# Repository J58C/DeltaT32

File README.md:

# DeltaT32 – ESP32-C3 Wearable for Capstone

**DeltaT32** is a modular hardware design project based on the **ESP32-C3 Mini-1**, intended primarily for wearable systems, but versatile enough for general-purpose embedded applications. Created using **KiCad 8**, this project includes a main ESP unit and two detachable sensor boards (BMI160/270 and MPU9250), making it ideal for both academic and practical applications.

This design has been created specifically to fulfill the requirements of a **Capstone Project**, integrating modern hardware design practices with real-world applications. Although firmware development is still pending, the hardware is designed to be compatible with the **[esp-rs (ESP32 Rust)](https://github.com/esp-rs)** ecosystem.

## Project Structure

```
DeltaT32/
├── Schematic/ # PDF-format schematics
├── Hardwares/
│ ├── esp-unit-c3-v3/ # KiCad project for the main ESP32-C3 board
│ ├── sensor-bmi-v2/ # KiCad project for the BMI160/270 sensor board
│ └── sensor-mpu-v2/ # KiCad project for the MPU9250 sensor board
├── 3DModels/ # 3D models of components (if available)
├── Archives/ # Archived ZIP files of older versions
├── Materials/ # Bill of Materials (BOM) for each board
└── README.md # Project documentation
````

## Technical Specifications

| Component      | Description                                  |
|----------------|----------------------------------------------|
| MCU            | ESP32-C3 Mini-1                              |
| Sensors        | BMI160/270, MPU9250 (modular and detachable) |
| Design Style   | Modular: separate mainboard and sensor units |
| CAD Tool       | KiCad 8                                      |
| Firmware       | Not included (hardware only)                 |
| Rust Support   | Designed with esp-rs compatibility in mind   |
| Outputs        | Schematics, BOMs, 3D Visuals        |

## Firmware Compatibility

This hardware is designed to be compatible with the **[esp-rs (Rust for ESP32)](https://github.com/esp-rs)** ecosystem, but **no actual firmware has been implemented or tested** using Rust at this time. Custom firmware development in C, C++, or Rust.

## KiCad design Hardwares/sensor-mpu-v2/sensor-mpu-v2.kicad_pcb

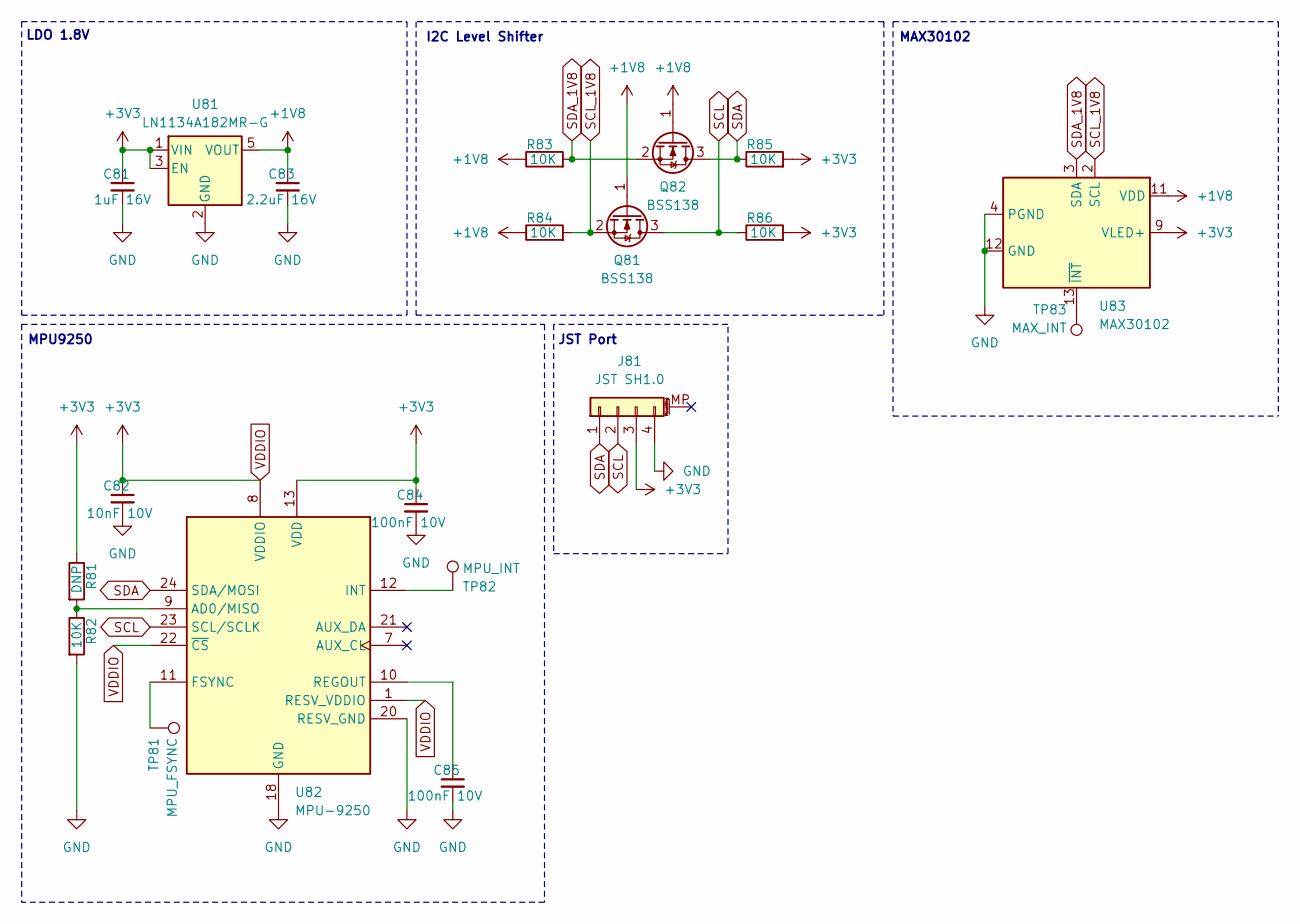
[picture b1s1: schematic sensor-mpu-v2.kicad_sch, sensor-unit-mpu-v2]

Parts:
C81: 1uF 16V; C_0603_1608Metric; LCSC C52923
C82: 10nF 10V; C_0603_1608Metric; LCSC C15195
C83: 2.2uF 16V; C_0603_1608Metric; LCSC C23630
C84, C85: 100nF 10V; C_0603_1608Metric; LCSC C1525
J81: JST SH1.0; JST_SH_BM04B-SRSS-TB_1x04-1MP_P1.00mm_Vertical
Q81, Q82: BSS138; SOT-23; LCSC C52895
R81: DNP; R_0402_1005Metric
R82, R83, R84, R85, R86: 10K; R_0402_1005Metric; LCSC C25744
TP81: MPU_FSYNC; TestPoint_Pad_D1.0mm
TP82: MPU_INT; TestPoint_Pad_D1.0mm
TP83: MAX_INT; TestPoint_Pad_D1.0mm
U81: LN1134A182MR-G; SOT-23-5; LCSC C141424
U82: MPU-9250; InvenSense_QFN-24_3x3mm_P0.4mm_NoMask
U83: MAX30102; Maxim_OLGA-14_3.3x5.6mm_P0.8mm

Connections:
+1V8: C83.1, Q81.1 (G), Q82.1 (G), R83.1, R84.1, U81.5 (VOUT), U83.11 (VDD)
GND: C81.2, C82.2, C83.2, C84.2, C85.2, J81.4, R82.2, U81.2 (GND), U82.18 (GND), U82.20 (RESV_GND), U83.4 (PGND), U83.12 (GND)
unnamed: R81.2, R82.1, U82.9 (AD0/MISO)
unnamed: TP81.1, U82.11 (FSYNC)
unnamed: TP82.1, U82.12 (INT)
unnamed: C85.1, U82.10 (REGOUT)
unnamed: TP83.1, U83.13 (~INT)
SCL: J81.2, Q81.3 (D), R86.1, U82.23 (SCL/SCLK)
SCL_1V8: Q81.2 (S), R84.2, U83.2 (SCL)
SDA: J81.1, Q82.3 (D), R85.1, U82.24 (SDA/MOSI)
SDA_1V8: Q82.2 (S), R83.2, U83.3 (SDA)
VDDIO: C81.1, C82.1, C84.1, J81.3, R81.1, R85.2, R86.2, U81.1 (VIN), U81.3 (EN), U82.1 (RESV_VDDIO), U82.8 (VDDIO), U82.13 (VDD), U82.22 (~CS), U83.9 (VLED+), U83.10 (VLED+)

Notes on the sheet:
I2C Level Shifter
MPU9250
MAX30102
JST Port
LDO 1.8V

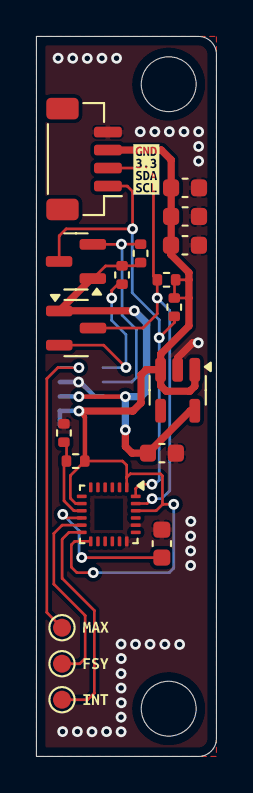
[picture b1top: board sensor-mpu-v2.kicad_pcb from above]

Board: 2 copper layers, 10.0 x 40.0 mm, 24 parts (1 on the bottom side), 12 nets.

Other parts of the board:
kibuzzard-680F6A44: G***; kibuzzard-680F6A44
kibuzzard-6817376F: G***; kibuzzard-6817376F
kibuzzard-6817407C: G***; kibuzzard-6817407C
kibuzzard-68174073: G***; kibuzzard-68174073

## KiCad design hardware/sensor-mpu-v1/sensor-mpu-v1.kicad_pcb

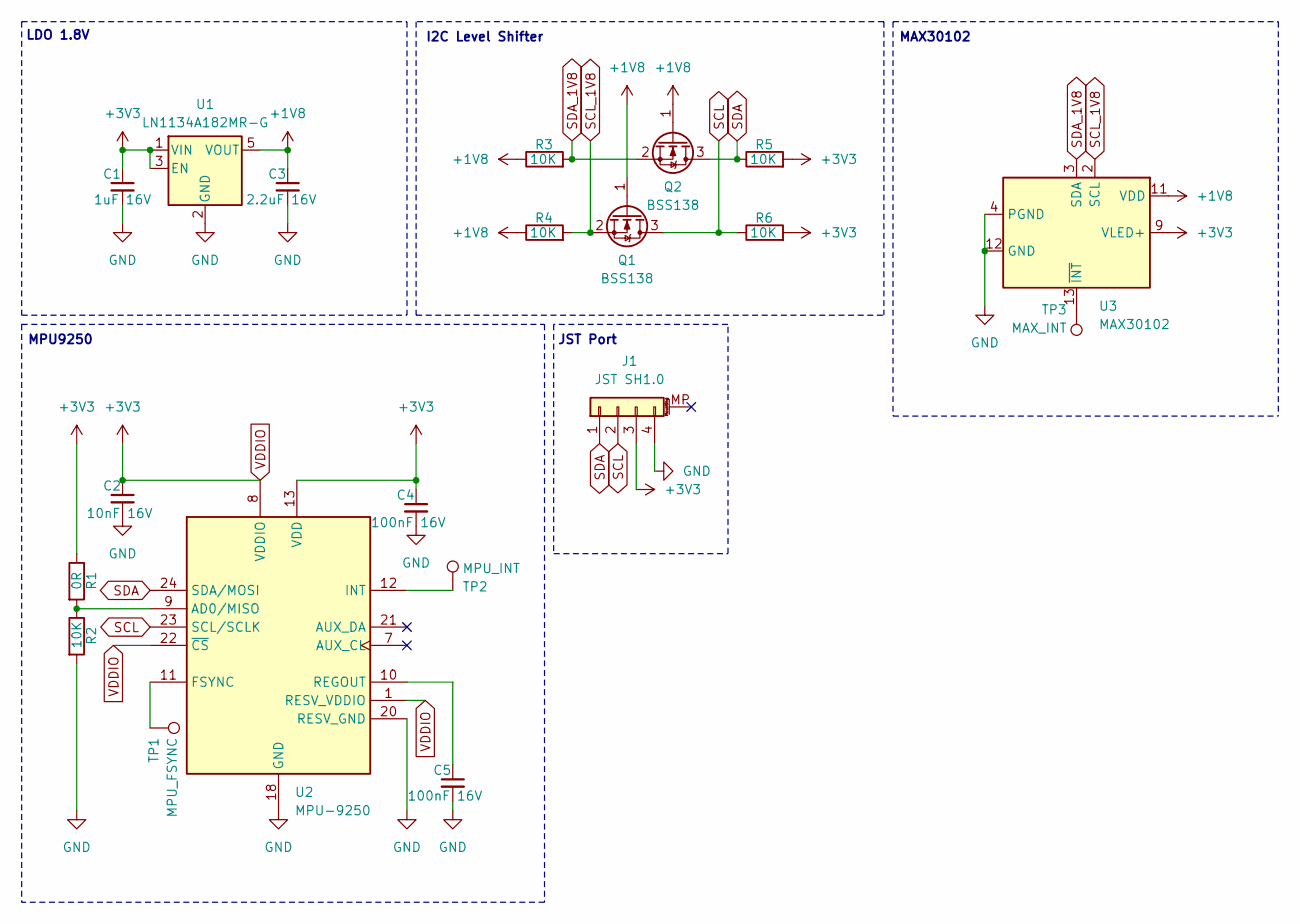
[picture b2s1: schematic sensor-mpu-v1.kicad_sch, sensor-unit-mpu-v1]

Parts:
C1: 1uF 16V; C_0603_1608Metric
C2: 10nF 16V; C_0603_1608Metric
C3: 2.2uF 16V; C_0603_1608Metric
C4, C5: 100nF 16V; C_0603_1608Metric
J1: JST SH1.0; JST_SH_SM04B-SRSS-TB_1x04-1MP_P1.00mm_Horizontal
Q1, Q2: BSS138; SOT-23
R1: 0R; R_0402_1005Metric
R2, R3, R4, R5, R6: 10K; R_0402_1005Metric
TP1: MPU_FSYNC; TestPoint_Pad_D1.0mm
TP2: MPU_INT; TestPoint_Pad_D1.0mm
TP3: MAX_INT; TestPoint_Pad_D1.0mm
U1: LN1134A182MR-G; SOT-23-5
U2: MPU-9250; InvenSense_QFN-24_3x3mm_P0.4mm_NoMask
U3: MAX30102; Maxim_OLGA-14_3.3x5.6mm_P0.8mm

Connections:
+1V8: C3.1, Q1.1 (G), Q2.1 (G), R3.1, R4.1, U1.5 (VOUT), U3.11 (VDD)
GND: C1.2, C2.2, C3.2, C4.2, C5.2, J1.4, R2.2, U1.2 (GND), U2.18 (GND), U2.20 (RESV_GND), U3.4 (PGND), U3.12 (GND)
unnamed: R1.2, R2.1, U2.9 (AD0/MISO)
unnamed: TP1.1, U2.11 (FSYNC)
unnamed: TP2.1, U2.12 (INT)
unnamed: C5.1, U2.10 (REGOUT)
unnamed: TP3.1, U3.13 (~INT)
SCL: J1.2, Q1.3 (D), R6.1, U2.23 (SCL/SCLK)
SCL_1V8: Q1.2 (S), R4.2, U3.2 (SCL)
SDA: J1.1, Q2.3 (D), R5.1, U2.24 (SDA/MOSI)
SDA_1V8: Q2.2 (S), R3.2, U3.3 (SDA)
VDDIO: C1.1, C2.1, C4.1, J1.3, R1.1, R5.2, R6.2, U1.1 (VIN), U1.3 (EN), U2.1 (RESV_VDDIO), U2.8 (VDDIO), U2.13 (VDD), U2.22 (~CS), U3.9 (VLED+), U3.10 (VLED+)

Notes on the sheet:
I2C Level Shifter
MPU9250
MAX30102
JST Port
LDO 1.8V

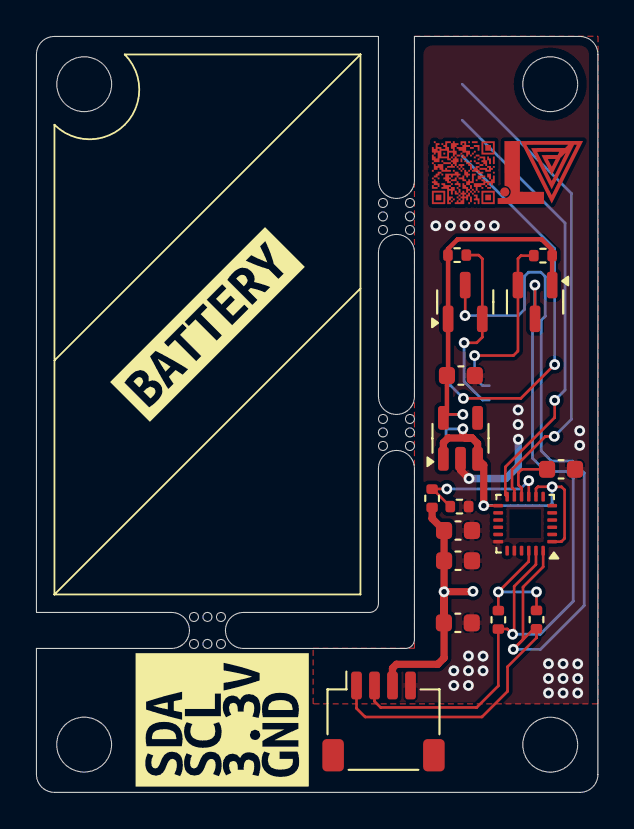
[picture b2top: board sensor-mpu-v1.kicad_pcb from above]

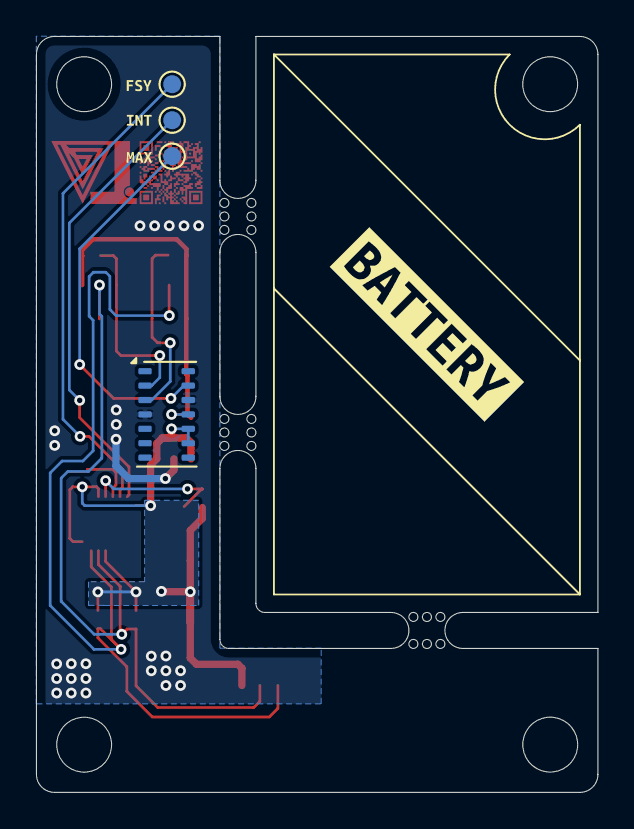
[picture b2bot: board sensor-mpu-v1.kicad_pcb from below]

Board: 2 copper layers, 31.2 x 42.0 mm, 29 parts (8 on the bottom side), 12 nets.

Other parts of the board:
kibuzzard-680F6B73: G***; kibuzzard-680F6B73
kibuzzard-680F6B94: G***; kibuzzard-680F6B94
kibuzzard-680F6BAF: G***; kibuzzard-680F6BAF
kibuzzard-680F686F: G***; kibuzzard-680F686F
kibuzzard-68103EF6, kibuzzard-68103EF6#2: G***; kibuzzard-68103EF6
mouse-bite-2mm-slot, mouse-bite-2mm-slot#2, mouse-bite-2mm-slot#3: VAL**; mouse-bite-2mm-slot

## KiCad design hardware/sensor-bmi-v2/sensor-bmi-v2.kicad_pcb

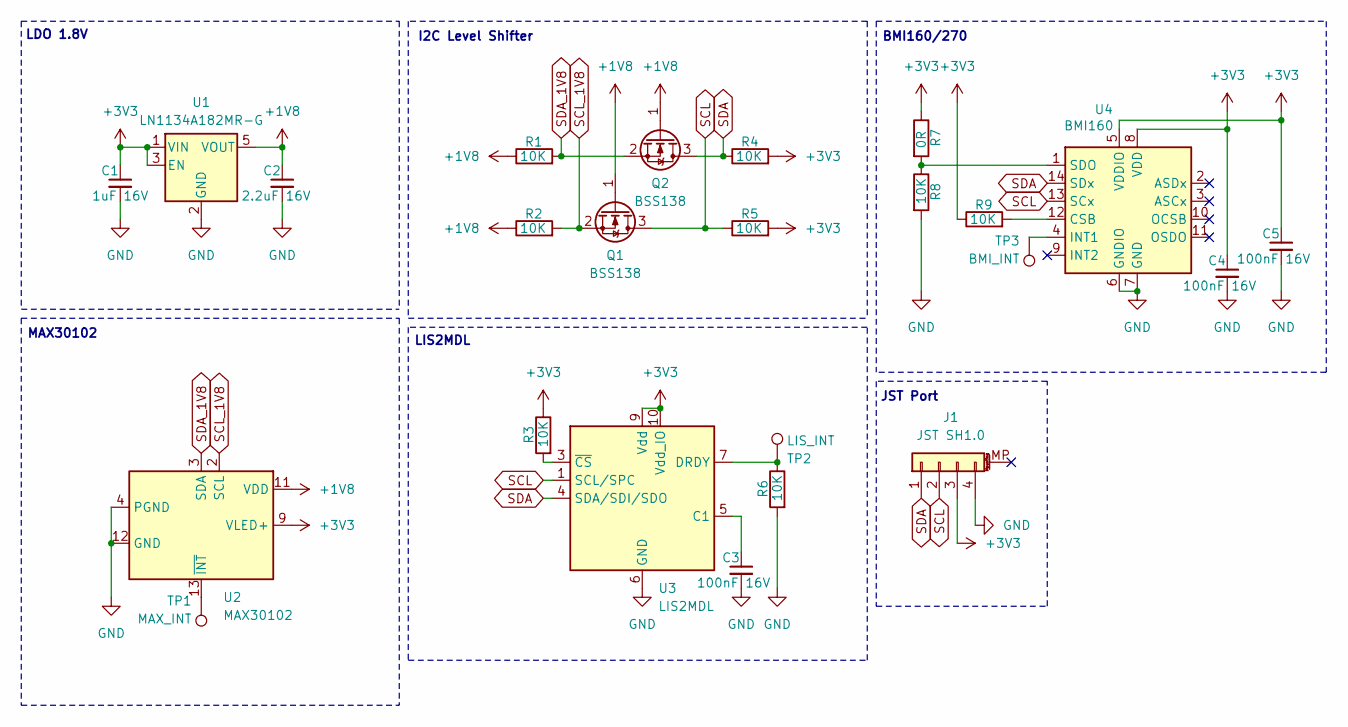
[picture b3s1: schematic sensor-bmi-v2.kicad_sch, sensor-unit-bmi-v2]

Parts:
C1: 1uF 16V; C_0603_1608Metric
C2: 2.2uF 16V; C_0603_1608Metric
C3, C4, C5: 100nF 16V; C_0603_1608Metric
J1: JST SH1.0; JST_SH_BM04B-SRSS-TB_1x04-1MP_P1.00mm_Vertical
Q1, Q2: BSS138; SOT-23
R1, R2, R3, R4, R5, R6, R8, R9: 10K; R_0402_1005Metric
R7: 0R; R_0402_1005Metric
TP1: MAX_INT; TestPoint_Pad_D1.0mm
TP2: LIS_INT; TestPoint_Pad_D1.0mm
TP3: BMI_INT; TestPoint_Pad_D1.0mm
U1: LN1134A182MR-G; SOT-23-5
U2: MAX30102; Maxim_OLGA-14_3.3x5.6mm_P0.8mm
U3: LIS2MDL; LGA-12_2x2mm_P0.5mm
U4: BMI160; Bosch_LGA-14_3x2.5mm_P0.5mm

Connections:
+1V8: C2.1, Q1.1 (G), Q2.1 (G), R1.1, R2.1, U1.5 (VOUT), U2.11 (VDD)
+3V3: C1.1, C4.1, C5.1, J1.3, R3.1, R4.2, R5.2, R7.1, R9.1, U1.1 (VIN), U1.3 (EN), U2.9 (VLED+), U2.10 (VLED+), U3.9 (Vdd), U3.10 (Vdd_IO), U4.5 (VDDIO), U4.8 (VDD)
GND: C1.2, C2.2, C3.2, C4.2, C5.2, J1.4, R6.2, R8.2, U1.2 (GND), U2.4 (PGND), U2.12 (GND), U3.6 (GND), U3.8 (GND), U4.6 (GNDIO), U4.7 (GND)
unnamed: TP1.1, U2.13 (~INT)
unnamed: C3.1, U3.5 (C1)
unnamed: R6.1, TP2.1, U3.7 (DRDY)
unnamed: R3.2, U3.3 (~CS)
unnamed: R9.2, U4.12 (CSB)
unnamed: TP3.1, U4.4 (INT1)
unnamed: R7.2, R8.1, U4.1 (SDO)
SCL: J1.2, Q1.3 (D), R5.1, U3.1 (SCL/SPC), U4.13 (SCx)
SCL_1V8: Q1.2 (S), R2.2, U2.2 (SCL)
SDA: J1.1, Q2.3 (D), R4.1, U3.4 (SDA/SDI/SDO), U4.14 (SDx)
SDA_1V8: Q2.2 (S), R1.2, U2.3 (SDA)

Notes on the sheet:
LDO 1.8V
MAX30102
JST Port
LIS2MDL
BMI160/270
I2C Level Shifter

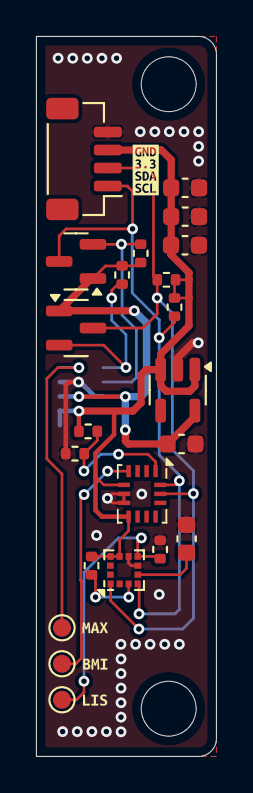
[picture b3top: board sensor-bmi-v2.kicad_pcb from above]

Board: 2 copper layers, 10.0 x 40.0 mm, 27 parts (1 on the bottom side), 13 nets.

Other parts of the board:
kibuzzard-680F6A2F: G***; kibuzzard-680F6A2F
kibuzzard-680F6A44: G***; kibuzzard-680F6A44
kibuzzard-680F69F9: G***; kibuzzard-680F69F9
kibuzzard-6817376F: G***; kibuzzard-6817376F

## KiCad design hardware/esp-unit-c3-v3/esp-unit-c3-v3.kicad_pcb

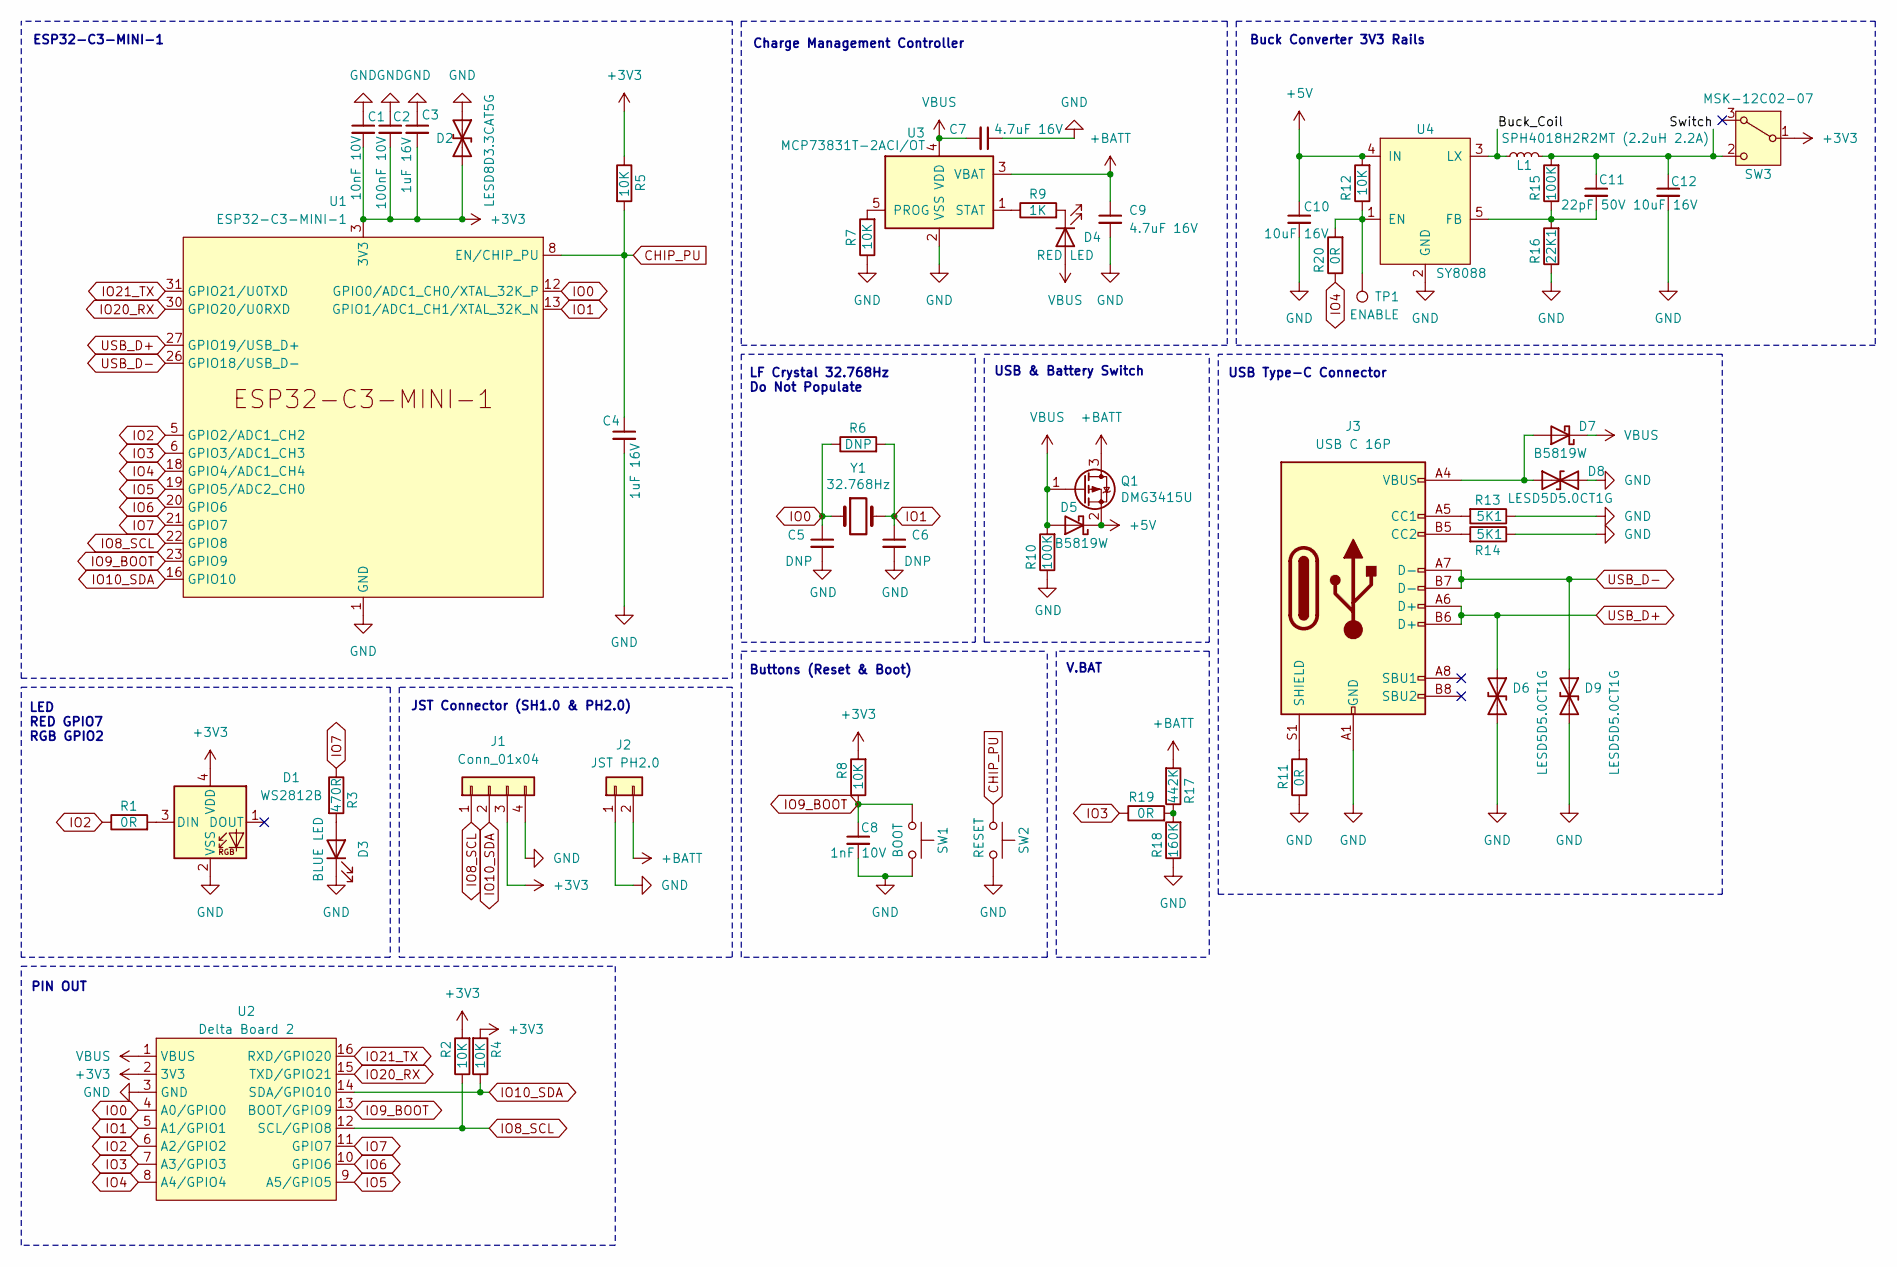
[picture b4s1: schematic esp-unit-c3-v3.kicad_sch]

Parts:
C1: 10nF 10V; C_0402_1005Metric; LCSC C15195
C2: 100nF 10V; C_0402_1005Metric; LCSC C1525
C3, C4: 1uF 16V; C_0402_1005Metric; LCSC C52923
C5, C6: DNP; C_0402_1005Metric
C7, C9: 4.7uF 16V; C_0603_1608Metric; LCSC C19666
C8: 1nF 10V; C_0402_1005Metric; LCSC C1523
C10, C12: 10uF 16V; C_0805_2012Metric; LCSC C15850
C11: 22pF 50V; C_0603_1608Metric; LCSC C1653
D1: WS2812B; LED_WS2812B-2020_PLCC4_2.0x2.0mm
D2: LESD8D3.3CAT5G; D_SOD-882; LCSC C172409
D3: BLUE LED; LED_0603_1608Metric; LCSC C2286
D4: RED LED; LED_0603_1608Metric; LCSC C2286
D5, D7: B5819W; D_SOD-123; LCSC C8598
D6, D8, D9: LESD5D5.0CT1G; D_SOD-523; LCSC C383211
J1: Conn_01x04; PinHeader_1x04_P1.00mm_Vertical
J2: JST PH2.0; JST_PH2.0
J3: USB C 16P; USB_C_Receptacle_GCT_USB4105-xx-A_16P_TopMnt_Horizontal
L1: SPH4018H2R2MT (2.2uH 2.2A); L_Bourns-SRN4018; LCSC C370436
Q1: DMG3415U; SOT-23; LCSC C96616
R1, R11, R19, R20: 0R; R_0402_1005Metric; LCSC C17168
R2, R4, R5, R7, R8, R12: 10K; R_0402_1005Metric; LCSC C25744
R3: 470R; R_0402_1005Metric; LCSC C25117
R6: DNP; R_0402_1005Metric
R9: 1K; R_0402_1005Metric; LCSC C11702
R10, R15: 100K; R_0402_1005Metric; LCSC C25741
R13, R14: 5K1; R_0402_1005Metric; LCSC C25905
R16: 22K1; R_0402_1005Metric; LCSC C43473
R17: 442K; R_0805_2012Metric
R18: 160K; R_0805_2012Metric
SW1: BOOT; SW_Push_SPST_NO_Alps_SKRK
SW2: RESET; SW_Push_SPST_NO_Alps_SKRK
SW3: MSK-12C02-07
TP1: ENABLE; TestPoint_Pad_D1.0mm
U1: ESP32-C3-MINI-1
U2: Delta Board 2; Delta_Board-2
U3: MCP73831T-2ACI/OT; SOT-23-5; LCSC C424093
U4: SY8088; SOT-23-5; LCSC C479072
Y1: 32.768Hz; Crystal_SMD_3215-2Pin_3.2x1.5mm

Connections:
+3V3: C1.2, C2.2, C3.2, D1.4 (VDD), D2.2 (A2), J1.3, R2.2, R4.2, R5.1, R8.2, SW3.1 (B), U1.3 (3V3), U2.2 (3V3)
+5V: C10.1, D5.1 (K), Q1.2 (S), R12.2, U4.4 (IN)
+BATT: C9.1, J2.2, Q1.3 (D), R17.2, U3.3 (VBAT)
/Buck_Coil: L1.1, U4.3 (LX)
/Switch: C11.1, C12.1, L1.2, R15.2, SW3.2 (C)
CHIP_PU: C4.1, R5.2, SW2.1, U1.8 (EN/CHIP_PU)
GND: C1.1, C2.1, C3.1, C4.2, C5.2, C6.2, C7.1, C8.2, C9.2, C10.2, C12.2, D1.2 (VSS), D2.1 (A1), D3.1 (K), D6.2 (A2), D8.2 (A2), D9.2 (A2), J1.4, J2.1, J3.A1 (GND), J3.A12 (GND), J3.B1 (GND), J3.B12 (GND), R7.1, R10.1, R11.1, R13.1, R14.1, R16.1, R18.1, SW1.2, SW2.2, U1.1 (GND), U1.2 (GND), U1.11 (GND), U1.14 (GND), U1.36 (GND), U1.37 (GND), U1.38 (GND), U1.39 (GND), U1.40 (GND), U1.41 (GND), U1.42 (GND), U1.43 (GND), U1.44 (GND), U1.45 (GND), U1.46 (GND), U1.47 (GND), U1.48 (GND), U1.49 (GND), U1.50 (GND), U1.51 (GND), U1.52 (GND), U1.53 (GND), U2.3 (GND), U3.2 (VSS), U4.2 (GND)
IO0: C5.1, R6.1, U1.12 (GPIO0/ADC1_CH0/XTAL_32K_P), U2.4 (A0/GPIO0), Y1.1
IO1: C6.1, R6.2, U1.13 (GPIO1/ADC1_CH1/XTAL_32K_N), U2.5 (A1/GPIO1), Y1.2
IO2: R1.1, U1.5 (GPIO2/ADC1_CH2), U2.6 (A2/GPIO2)
IO3: R19.1, U1.6 (GPIO3/ADC1_CH3), U2.7 (A3/GPIO3)
IO4: R20.1, U1.18 (GPIO4/ADC1_CH4), U2.8 (A4/GPIO4)
IO5: U1.19 (GPIO5/ADC2_CH0), U2.9 (A5/GPIO5)
IO6: U1.20 (GPIO6), U2.10 (GPIO6)
IO7: R3.1, U1.21 (GPIO7), U2.11 (GPIO7)
IO8_SCL: J1.1, R2.1, U1.22 (GPIO8), U2.12 (SCL/GPIO8)
IO9_BOOT: C8.1, R8.1, SW1.1, U1.23 (GPIO9), U2.13 (BOOT/GPIO9)
IO10_SDA: J1.2, R4.1, U1.16 (GPIO10), U2.14 (SDA/GPIO10)
IO20_RX: U1.30 (GPIO20/U0RXD), U2.15 (TXD/GPIO21)
IO21_TX: U1.31 (GPIO21/U0TXD), U2.16 (RXD/GPIO20)
unnamed: D1.3 (DIN), R1.2
unnamed: D3.2 (A), R3.2
unnamed: D4.1 (K), R9.2
unnamed: D7.2 (A), D8.1 (A1), J3.A4 (VBUS), J3.A9 (VBUS), J3.B4 (VBUS), J3.B9 (VBUS)
unnamed: J3.A5 (CC1), R13.2
unnamed: J3.B5 (CC2), R14.2
unnamed: J3.S1 (SHIELD), R11.2
unnamed: R17.1, R18.2, R19.2
unnamed: R7.2, U3.5 (PROG)
unnamed: R9.1, U3.1 (STAT)
unnamed: R12.1, R20.2, TP1.1, U4.1 (EN)
unnamed: C11.2, R15.1, R16.2, U4.5 (FB)
USB_D+: D6.1 (A1), J3.A6 (D+), J3.B6 (D+), U1.27 (GPIO19/USB_D+)
USB_D-: D9.1 (A1), J3.A7 (D-), J3.B7 (D-), U1.26 (GPIO18/USB_D-)
VBUS: C7.2, D4.2 (A), D5.2 (A), D7.1 (K), Q1.1 (G), R10.2, U2.1 (VBUS), U3.4 (VDD)

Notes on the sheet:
LED RED GPIO7 RGB GPIO2
LF Crystal 32.768Hz Do Not Populate
JST Connector (SH1.0 & PH2.0)
Charge Management Controller
PIN OUT
Buck Converter 3V3 Rails
USB & Battery Switch
Buttons (Reset & Boot)
V.BAT
USB Type-C Connector
ESP32-C3-MINI-1

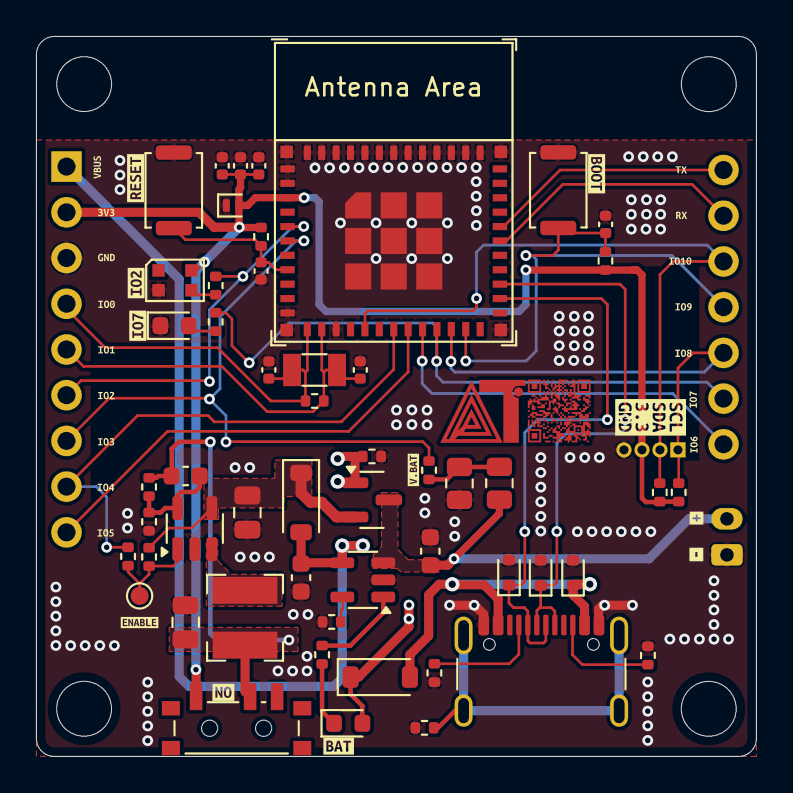
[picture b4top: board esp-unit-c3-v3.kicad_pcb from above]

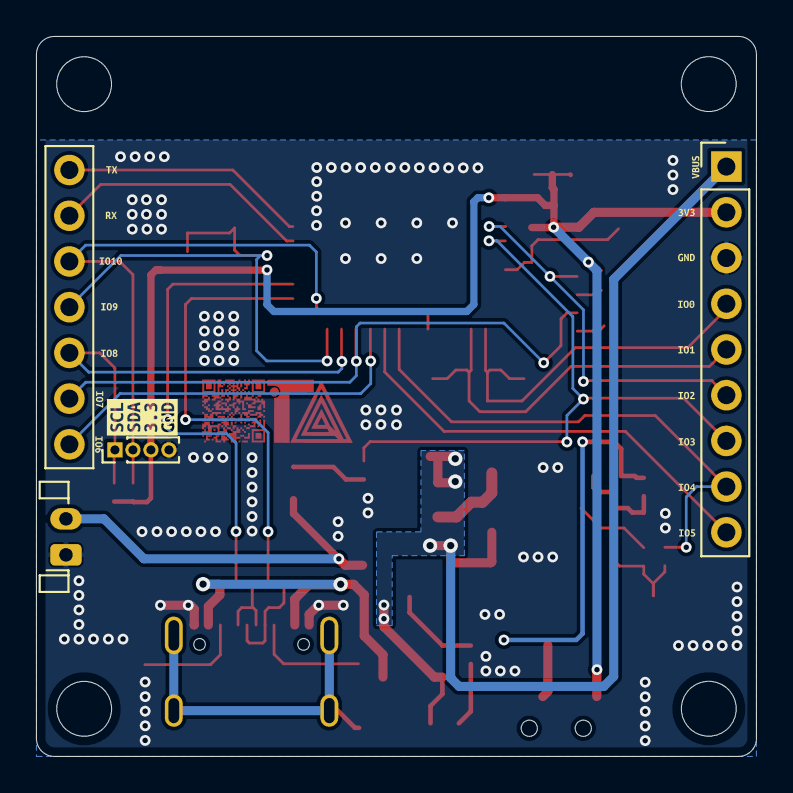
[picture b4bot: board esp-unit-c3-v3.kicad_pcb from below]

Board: 2 copper layers, 40.0 x 40.0 mm, 99 parts (19 on the bottom side), 35 nets.

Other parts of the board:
kibuzzard-680CD9B9: G***; kibuzzard-680CD9B9
kibuzzard-680CD9CB: G***; kibuzzard-680CD9CB
kibuzzard-680CDA1E: G***; kibuzzard-680CDA1E
kibuzzard-680CDA08: G***; kibuzzard-680CDA08
kibuzzard-680CDA64: G***; kibuzzard-680CDA64
kibuzzard-680CDAE0: G***; kibuzzard-680CDAE0
kibuzzard-680CDBCC: G***; kibuzzard-680CDBCC
kibuzzard-680CDBED: G***; kibuzzard-680CDBED
kibuzzard-680CDFA2: G***; kibuzzard-680CDFA2
kibuzzard-680CFCF0, kibuzzard-680CFCF0#2: G***; kibuzzard-680CFCF0
kibuzzard-680CFD7F, kibuzzard-680CFD7F#2: G***; kibuzzard-680CFD7F
kibuzzard-680CFD12, kibuzzard-680CFD12#2: G***; kibuzzard-680CFD12
kibuzzard-680CFD73, kibuzzard-680CFD73#2: G***; kibuzzard-680CFD73
kibuzzard-680CFDA8, kibuzzard-680CFDA8#2: G***; kibuzzard-680CFDA8
kibuzzard-680CFDBB, kibuzzard-680CFDBB#2: G***; kibuzzard-680CFDBB
kibuzzard-680CFDCF, kibuzzard-680CFDCF#2: G***; kibuzzard-680CFDCF
kibuzzard-680CFDE4, kibuzzard-680CFDE4#2: G***; kibuzzard-680CFDE4
kibuzzard-680CFDFB, kibuzzard-680CFDFB#2: G***; kibuzzard-680CFDFB
kibuzzard-680CFE08, kibuzzard-680CFE08#2: G***; kibuzzard-680CFE08
kibuzzard-680CFF32: G***; kibuzzard-680CFF32
kibuzzard-6816DD82, kibuzzard-6816DD82#2: G***; kibuzzard-6816DD82
kibuzzard-6816DDEA, kibuzzard-6816DDEA#2: G***; kibuzzard-6816DDEA
kibuzzard-6816DDFD, kibuzzard-6816DDFD#2: G***; kibuzzard-6816DDFD
kibuzzard-6816DE5B, kibuzzard-6816DE5B#2: G***; kibuzzard-6816DE5B
kibuzzard-6816DE78, kibuzzard-6816DE78#2: G***; kibuzzard-6816DE78
kibuzzard-6816DE97, kibuzzard-6816DE97#2: G***; kibuzzard-6816DE97
kibuzzard-6816EC1C, kibuzzard-6816EC1C#2: G***; kibuzzard-6816EC1C

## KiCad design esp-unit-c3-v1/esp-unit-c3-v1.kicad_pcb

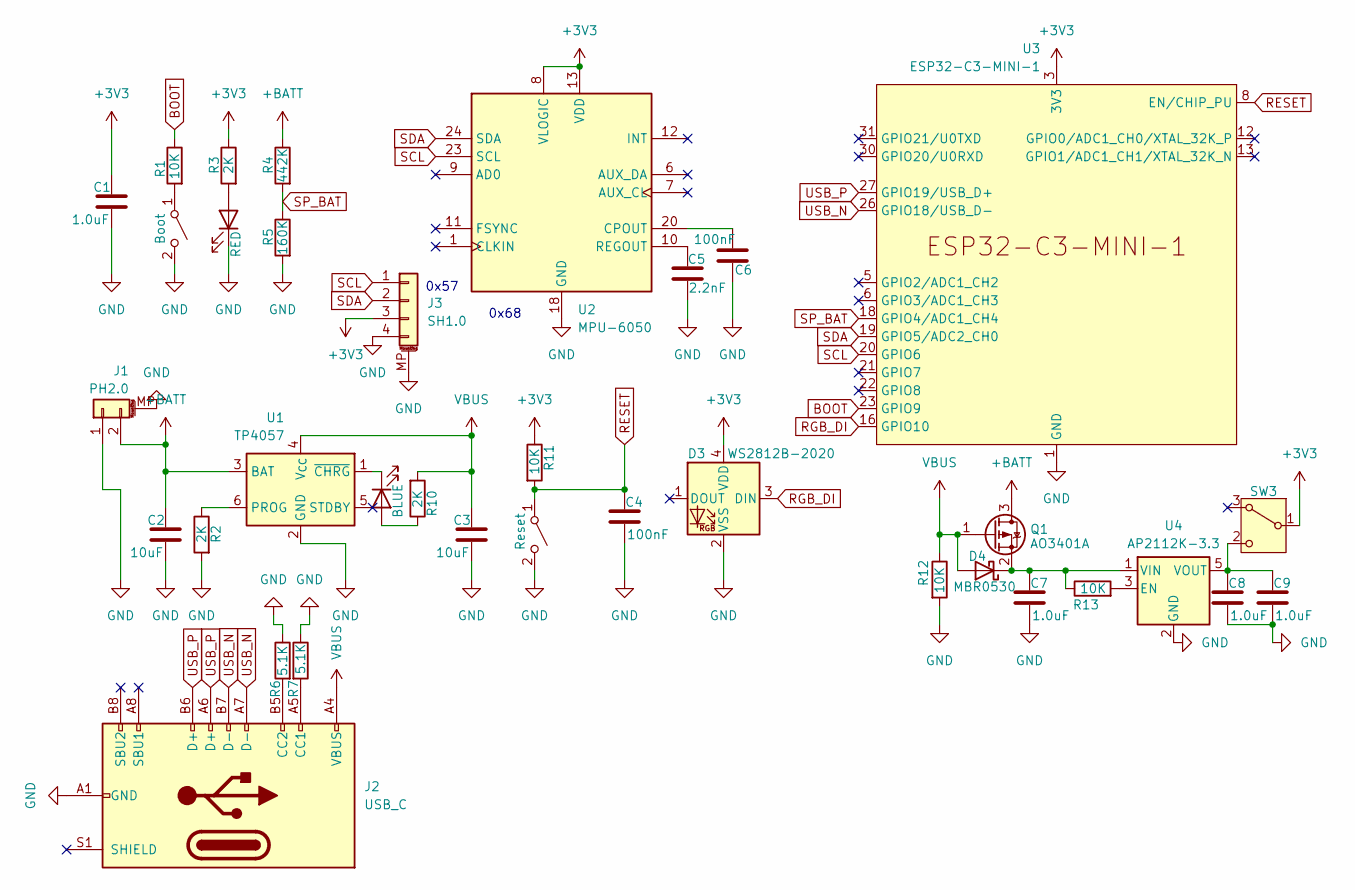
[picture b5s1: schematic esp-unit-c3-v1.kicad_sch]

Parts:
C1, C7, C8, C9: 1.0uF; C_0402_1005Metric
C2, C3: 10uF; C_0402_1005Metric
C4, C6: 100nF; C_0402_1005Metric
C5: 2.2nF; C_0603_1608Metric
D1: RED; LED_0402_1005Metric
D2: BLUE; LED_0402_1005Metric
D3: WS2812B-2020; LED_WS2812B-2020_PLCC4_2.0x2.0mm
D4: MBR0530; D_SOD-123
J1: PH2.0; JST_PH_B2B-PH-SM4-TB_1x02-1MP_P2.00mm_Vertical
J2: USB_C; USB_C_Receptacle_GCT_USB4110
J3: SH1.0; JST_SH_BM04B-SRSS-TB_1x04-1MP_P1.00mm_Vertical
Q1: AO3401A; SOT-23
R1, R11, R12, R13: 10K; R_0402_1005Metric
R2, R3, R10: 2K; R_0402_1005Metric
R4: 442K; R_0805_2012Metric
R5: 160K; R_0805_2012Metric
R6, R7: 5.1K; R_0402_1005Metric
SW1: Boot; SW_Push_SPST_NO_Alps_SKRK
SW2: Reset; SW_Push_SPST_NO_Alps_SKRK
SW3: SW_SPDT_312; SW_SPDT_PCM12
U1: TP4057; TSOT-23-6
U2: MPU-6050; InvenSense_QFN-24_4x4mm_P0.5mm
U3: ESP32-C3-MINI-1
U4: AP2112K-3.3; SOT-23-5

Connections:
+3V3: C1.1, D3.4 (VDD), J3.3, R3.1, R11.1, SW3.1 (B), U2.8 (VLOGIC), U2.13 (VDD), U3.3 (3V3)
+BATT: C2.1, J1.2, Q1.3 (D), R4.1, U1.3 (BAT)
BOOT: R1.1, U3.23 (GPIO9)
GND: C1.2, C2.2, C3.2, C4.2, C5.1, C6.2, C7.2, C8.2, C9.2, D1.1 (K), D3.2 (VSS), J1.1, J1.MP (MountPin), J2.A1 (GND), J2.A12 (GND), J2.B1 (GND), J2.B12 (GND), J3.4, J3.MP (MountPin), R2.2, R5.2, R6.1, R7.1, R12.2, SW1.2 (B), SW2.2 (B), U1.2 (GND), U2.18 (GND), U3.1 (GND), U3.2 (GND), U3.11 (GND), U3.14 (GND), U3.36 (GND), U3.37 (GND), U3.38 (GND), U3.39 (GND), U3.40 (GND), U3.41 (GND), U3.42 (GND), U3.43 (GND), U3.44 (GND), U3.45 (GND), U3.46 (GND), U3.47 (GND), U3.48 (GND), U3.49 (GND), U3.50 (GND), U3.51 (GND), U3.52 (GND), U3.53 (GND), U4.2 (GND)
unnamed: D1.2 (A), R3.2
unnamed: D2.2 (A), R10.1
unnamed: D2.1 (K), U1.1 (~CHRG)
unnamed: C7.1, D4.1 (K), Q1.2 (S), R13.1, U4.1 (VIN)
unnamed: J2.A5 (CC1), R7.2
unnamed: J2.B5 (CC2), R6.2
unnamed: R1.2, SW1.1 (A)
unnamed: C8.1, C9.1, SW3.2 (C), U4.5 (VOUT)
unnamed: R2.1, U1.6 (PROG)
unnamed: C6.1, U2.20 (CPOUT)
unnamed: C5.2, U2.10 (REGOUT)
unnamed: R13.2, U4.3 (EN)
RESET: C4.1, R11.2, SW2.1 (A), U3.8 (EN/CHIP_PU)
RGB_DI: D3.3 (DIN), U3.16 (GPIO10)
SCL: J3.1, U2.23 (SCL), U3.20 (GPIO6)
SDA: J3.2, U2.24 (SDA), U3.19 (GPIO5/ADC2_CH0)
SP_BAT: R4.2, R5.1, U3.18 (GPIO4/ADC1_CH4)
USB_N: J2.A7 (D-), J2.B7 (D-), U3.26 (GPIO18/USB_D-)
USB_P: J2.A6 (D+), J2.B6 (D+), U3.27 (GPIO19/USB_D+)
VBUS: C3.1, D4.2 (A), J2.A4 (VBUS), J2.A9 (VBUS), J2.B4 (VBUS), J2.B9 (VBUS), Q1.1 (G), R10.2, R12.1, U1.4 (V_{CC})

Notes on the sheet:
0x57
0x68

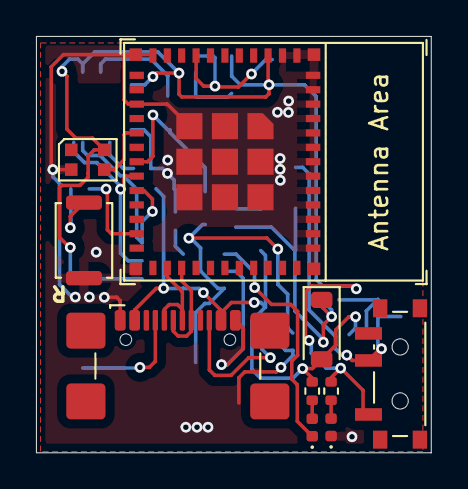
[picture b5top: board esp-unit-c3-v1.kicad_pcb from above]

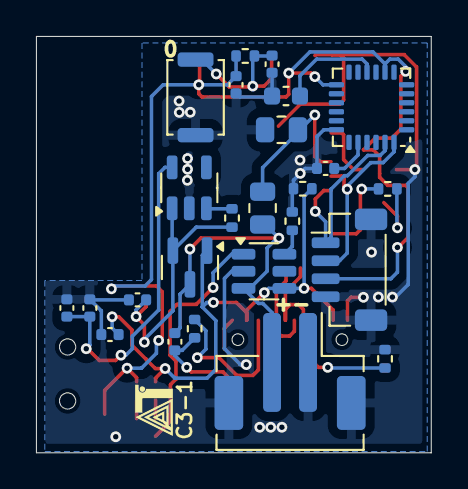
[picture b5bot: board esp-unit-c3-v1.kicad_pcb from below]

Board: 2 copper layers, 21.9 x 23.1 mm, 35 parts (25 on the bottom side), 24 nets.

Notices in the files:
README.md:
License: MIT
